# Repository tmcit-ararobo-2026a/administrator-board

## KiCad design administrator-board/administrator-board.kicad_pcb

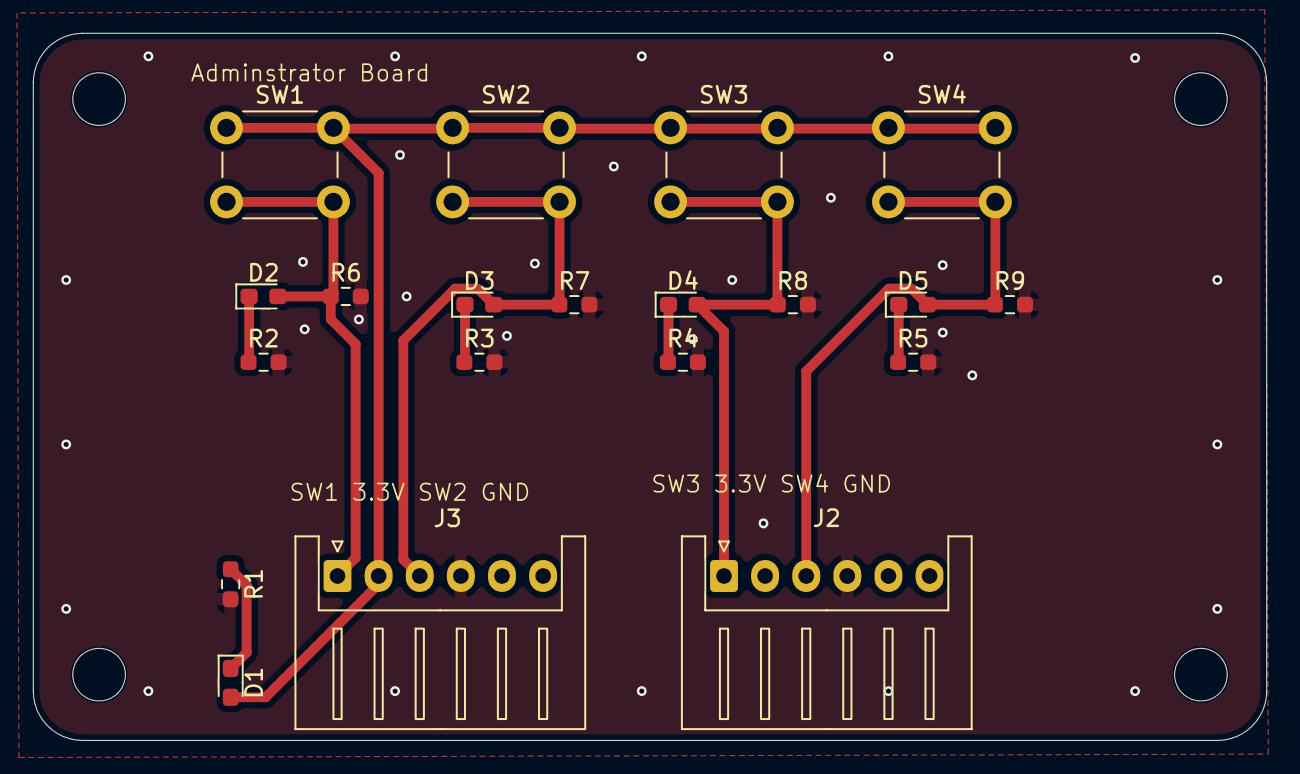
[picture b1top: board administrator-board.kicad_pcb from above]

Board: 2 copper layers, 75.0 x 43.0 mm, 20 parts (0 on the bottom side), 11 nets.

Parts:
D1, D2, D3, D4, D5: LED; LED_0603_1608Metric_Pad1.05x0.95mm_HandSolder
J2, J3: Conn_01x06; JST_XH_S6B-XH-A_1x06_P2.50mm_Horizontal
R1, R2, R3, R4, R5: 1k; R_0603_1608Metric_Pad0.98x0.95mm_HandSolder
R6, R7, R8, R9: 20k; R_0603_1608Metric_Pad0.98x0.95mm_HandSolder
SW1, SW2, SW3, SW4: SW_Push; SW_PUSH_6mm

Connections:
+3.3V: D1.2 (A), J3.2, SW1.1, SW2.1, SW3.1, SW4.1
GND: J2.4, J3.4, R1.2, R2.2, R3.2, R4.2, R5.2, R6.2, R7.2, R8.2, R9.2
unnamed: D1.1 (K), R1.1
unnamed: D2.1 (K), R2.1
unnamed: D3.1 (K), R3.1
unnamed: D4.1 (K), R4.1
unnamed: D5.1 (K), R5.1
SW1: D2.2 (A), J3.1, R6.1, SW1.2
SW2: D3.2 (A), J3.3, R7.1, SW2.2
SW3: D4.2 (A), J2.1, R8.1, SW3.2
SW4: D5.2 (A), J2.3, R9.1, SW4.2
